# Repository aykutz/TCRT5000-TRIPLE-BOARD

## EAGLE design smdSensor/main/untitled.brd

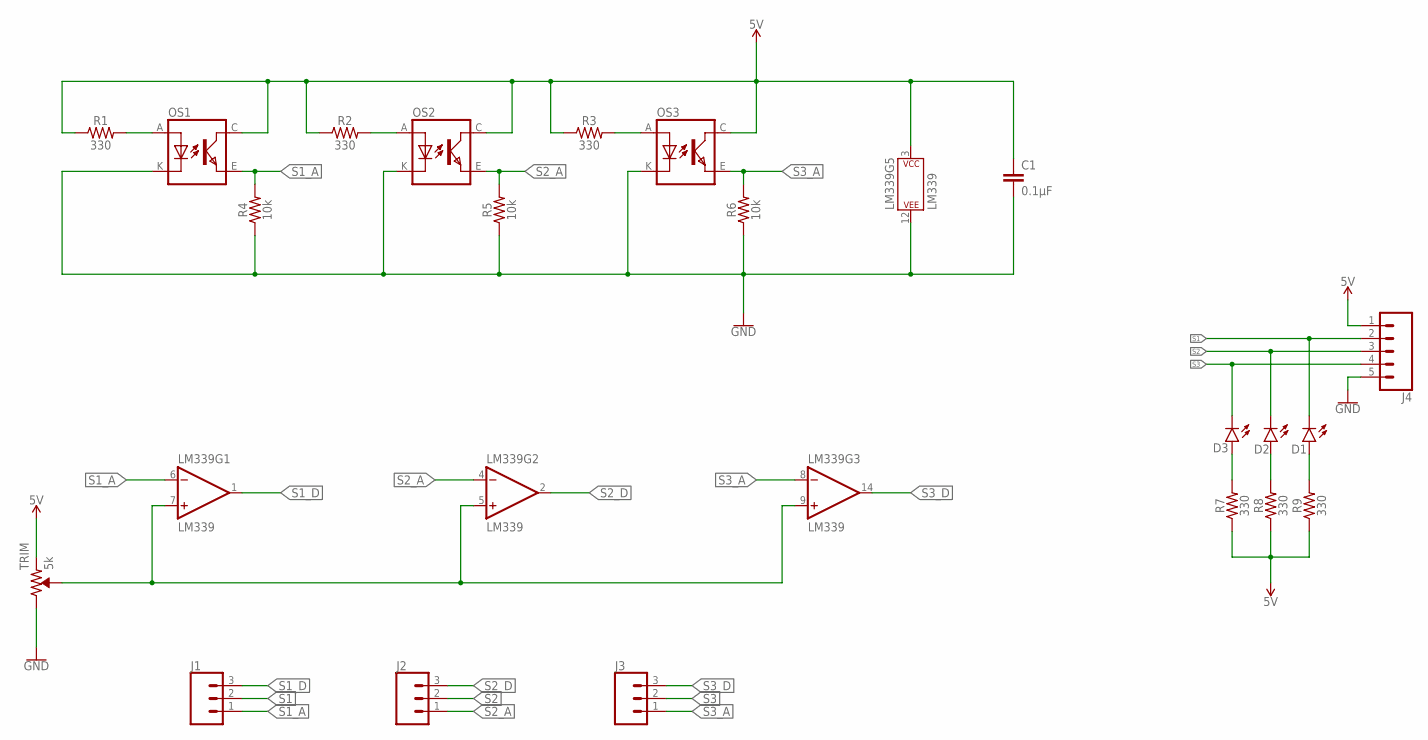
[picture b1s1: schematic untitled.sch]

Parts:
C1: 0.1µF; 0805
D1, D2, D3: LED-RED-0805; LED-0805
J1, J2, J3: CONN_03; 1X03
J4: CONN_05PTH; 1X05
LM339: LM339; TSSOP-14
OS1, OS2, OS3: TCRT5000
R1, R2, R3, R7, R8, R9: 330; 0805
R4, R5, R6: 10k; 0805
TRIM: 5k; TRIMPOT-SMD-5MM

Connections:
5V: C1.1, J4.1, LM339.3 (P$V+), OS1.C (COLLECTOR), OS2.C (COLLECTOR), OS3.C (COLLECTOR), R1.1, R2.1, R3.1, R7.1, R8.1, R9.1, TRIM.A (CCW)
GND: C1.2, J4.5, LM339.12 (P$V-), OS1.K (CATHODE), OS2.K (CATHODE), OS3.K (CATHODE), R4.1, R5.1, R6.1, TRIM.C (CW)
unnamed: OS1.A (ANODE), R1.2
unnamed: OS2.A (ANODE), R2.2
unnamed: OS3.A (ANODE), R3.2
unnamed: LM339.5 (+IN), LM339.7 (+IN), LM339.9 (+IN), TRIM.B (WIPER)
unnamed: D3.A, R7.2
unnamed: D2.A, R8.2
unnamed: D1.A, R9.2
S1: D1.C, J1.2, J4.2
S1_A: J1.1, LM339.6 (-IN), OS1.E (EMITTER), R4.2
S1_D: J1.3, LM339.1 (OUT)
S2: D2.C, J2.2, J4.3
S2_A: J2.1, LM339.4 (-IN), OS2.E (EMITTER), R5.2
S2_D: J2.3, LM339.2 (OUT)
S3: D3.C, J3.2, J4.4
S3_A: J3.1, LM339.8 (-IN), OS3.E (EMITTER), R6.2
S3_D: J3.3, LM339.14 (OUT)

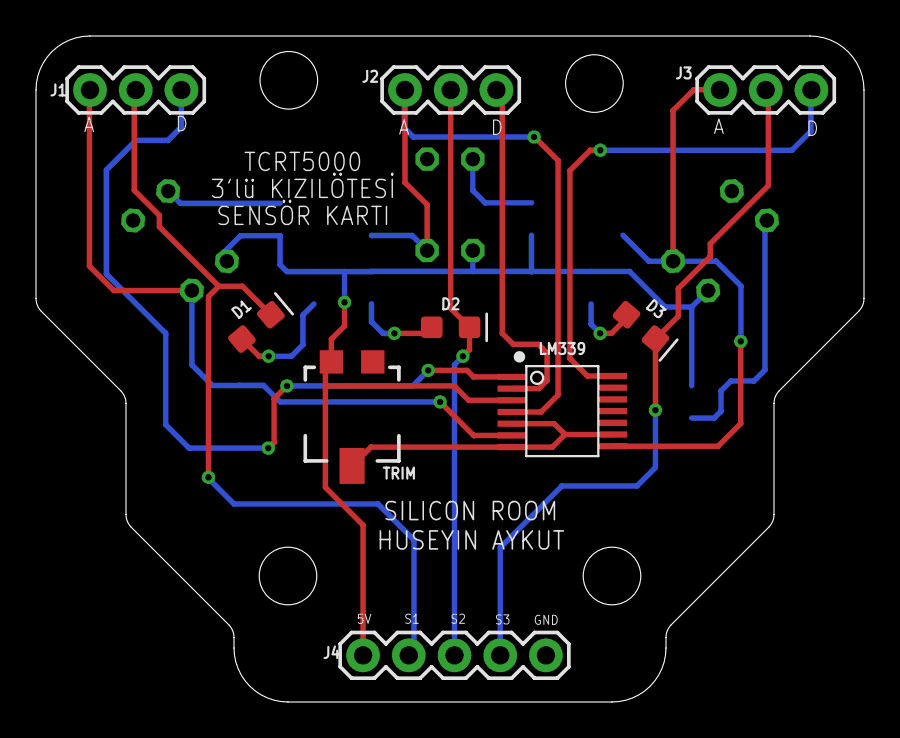
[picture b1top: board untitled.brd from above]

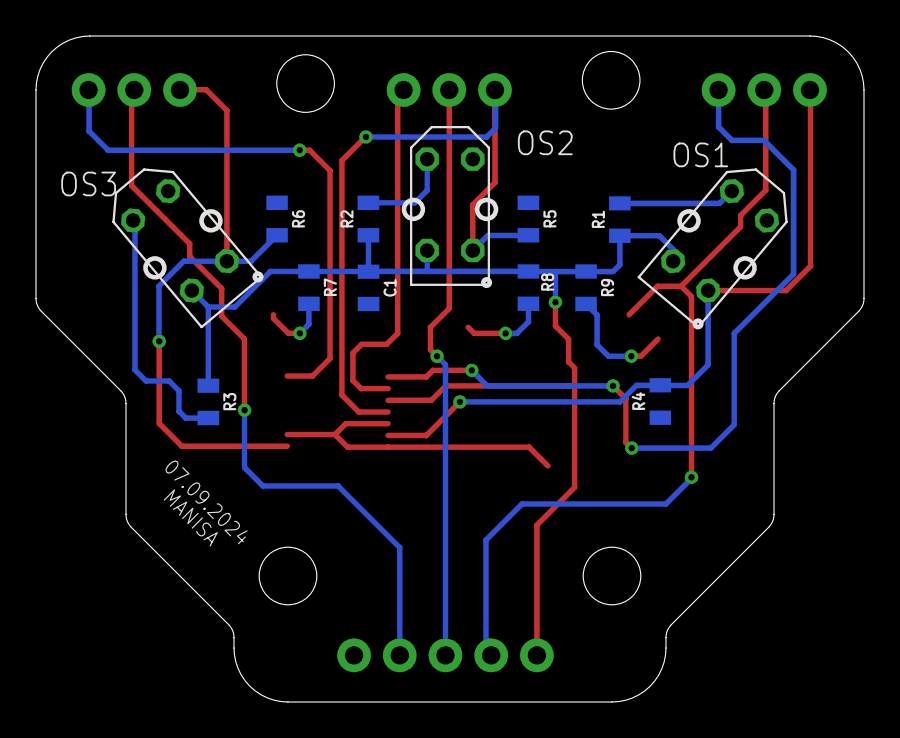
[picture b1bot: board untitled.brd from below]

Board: 2 copper layers, 46.0 x 37.0 mm, 22 parts (13 on the bottom side), 18 nets.

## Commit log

2024-09-07 TCRT5000-TRIPLE-BOARD

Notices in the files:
parts and their libraries:
SparkFun-Resistors: Licensing: Creative Commons ShareAlike 4.0 International - https://creativecommons.org/licenses/by-sa/4.0
